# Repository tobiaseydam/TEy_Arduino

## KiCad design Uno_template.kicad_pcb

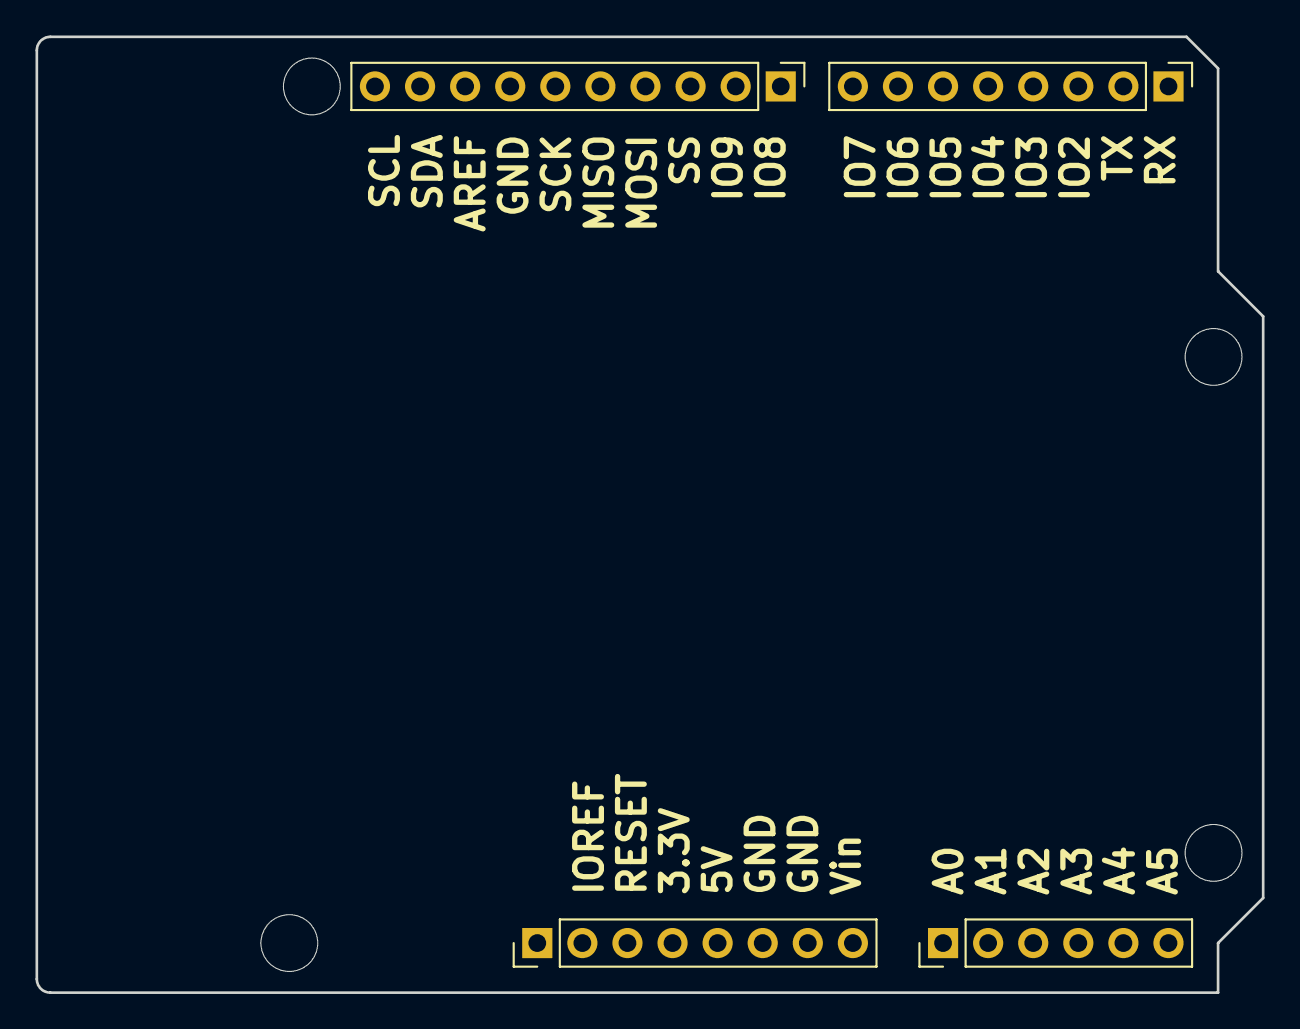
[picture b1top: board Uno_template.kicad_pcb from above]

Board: 2 copper layers, 69.1 x 53.8 mm, 4 parts (0 on the bottom side), 3 nets, no tracks yet.

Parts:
J1: POWER; Pin_Header_Straight_1x08_Pitch2.54mm
J2: ANALOG IN; Pin_Header_Straight_1x06_Pitch2.54mm
J3: IOH; Pin_Header_Straight_1x10_Pitch2.54mm
J4: IOL; Pin_Header_Straight_1x08_Pitch2.54mm

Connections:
/A4: J2.5, J3.9
/A5: J2.6, J3.10
GND: J1.6, J1.7, J3.7

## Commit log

2018-01-03 Schaltplan: Pins hinzugefügt
2018-01-03 Board: hinzugefügt
2018-01-04 Schaltplan: 1Wire interface added
